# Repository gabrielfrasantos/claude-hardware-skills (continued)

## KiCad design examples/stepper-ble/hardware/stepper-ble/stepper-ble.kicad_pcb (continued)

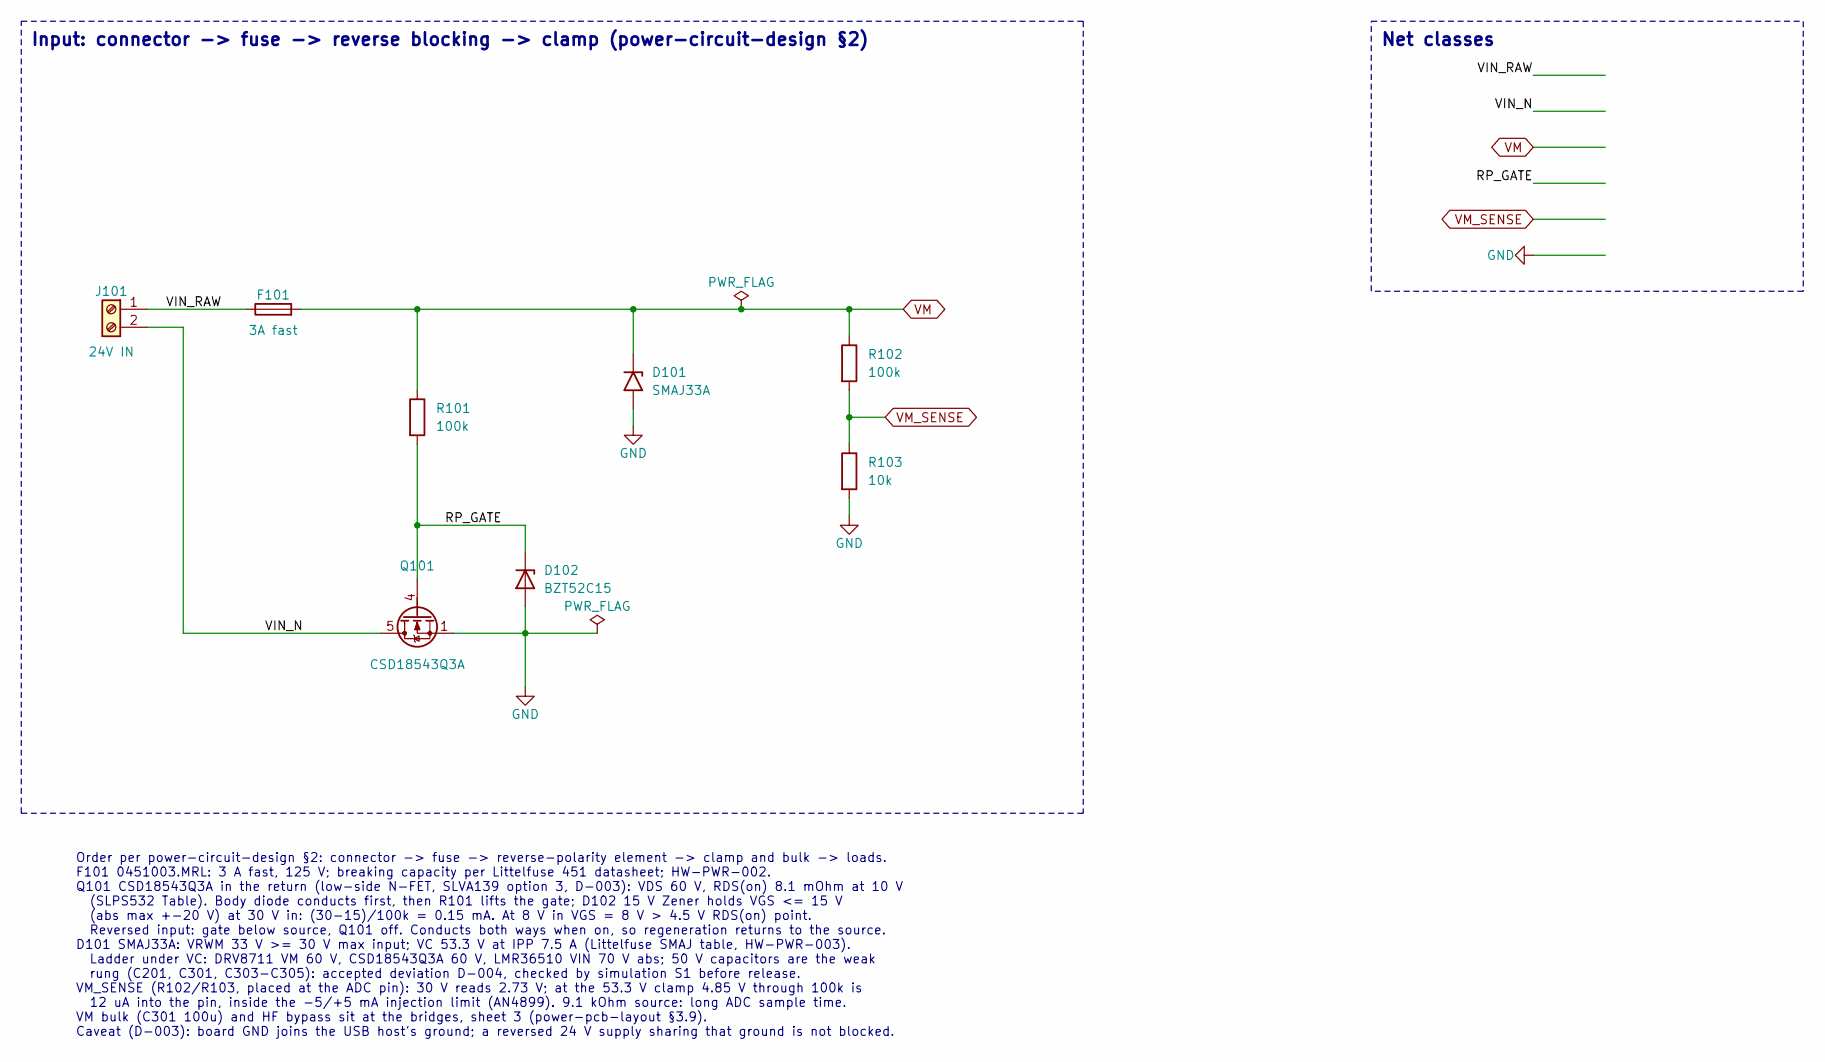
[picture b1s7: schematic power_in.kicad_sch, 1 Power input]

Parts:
D101: SMAJ33A; D_SMA; MPN SMAJ33A; LCSC C353454
D102: BZT52C15; D_SOD-123; MPN BZT52C15; LCSC C173427
F101: 3A fast; Fuse_Littelfuse-NANO2-451_453; Voltage 125V; MPN 0451003.MRL; LCSC C13982
J101: 24V IN; TerminalBlock_Phoenix_MKDS-1,5-2-5.08_1x02_P5.08mm_Horizont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; MPN 1715721; LCSC C480516
Q101: CSD18543Q3A; VSON-8_3.3x3.3mm_P0.65mm_NexFET_TI-land; Voltage 60V; MPN CSD18543Q3A; LCSC C840100
R101, R102: 100k; R_0402_1005Metric; MPN 0402WGF1003TCE; LCSC C25741
R103: 10k; R_0402_1005Metric; MPN 0402WGF1002TCE; LCSC C25744

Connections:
/1 Power input/RP_GATE: D102.1 (K), Q101.4 (G), R101.2
/1 Power input/VIN_N: J101.2, Q101.5 (D)
/1 Power input/VIN_RAW: F101.1, J101.1
GND: D101.2 (A2), D102.2 (A), Q101.1 (S), Q101.2 (S), Q101.3 (S), R103.2; also elsewhere on the board
VM: D101.1 (A1), F101.2, R101.1, R102.1; also elsewhere on the board
VM_SENSE: R102.2, R103.1; also elsewhere on the board

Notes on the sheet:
Input: connector -> fuse -> reverse blocking -> clamp (power-circuit-design §2)
Net classes
Order per power-circuit-design §2: connector -> fuse -> reverse-polarity element -> clamp and bulk -> loads. F101 0451003.MRL: 3 A fast, 125 V; breaking capacity per Littelfuse 451 datasheet; HW-PWR-002. Q101 CSD18543Q3A in the return (low-side N-FET, SLVA139 option 3, D-003): VDS 60 V, RDS(on) 8.1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

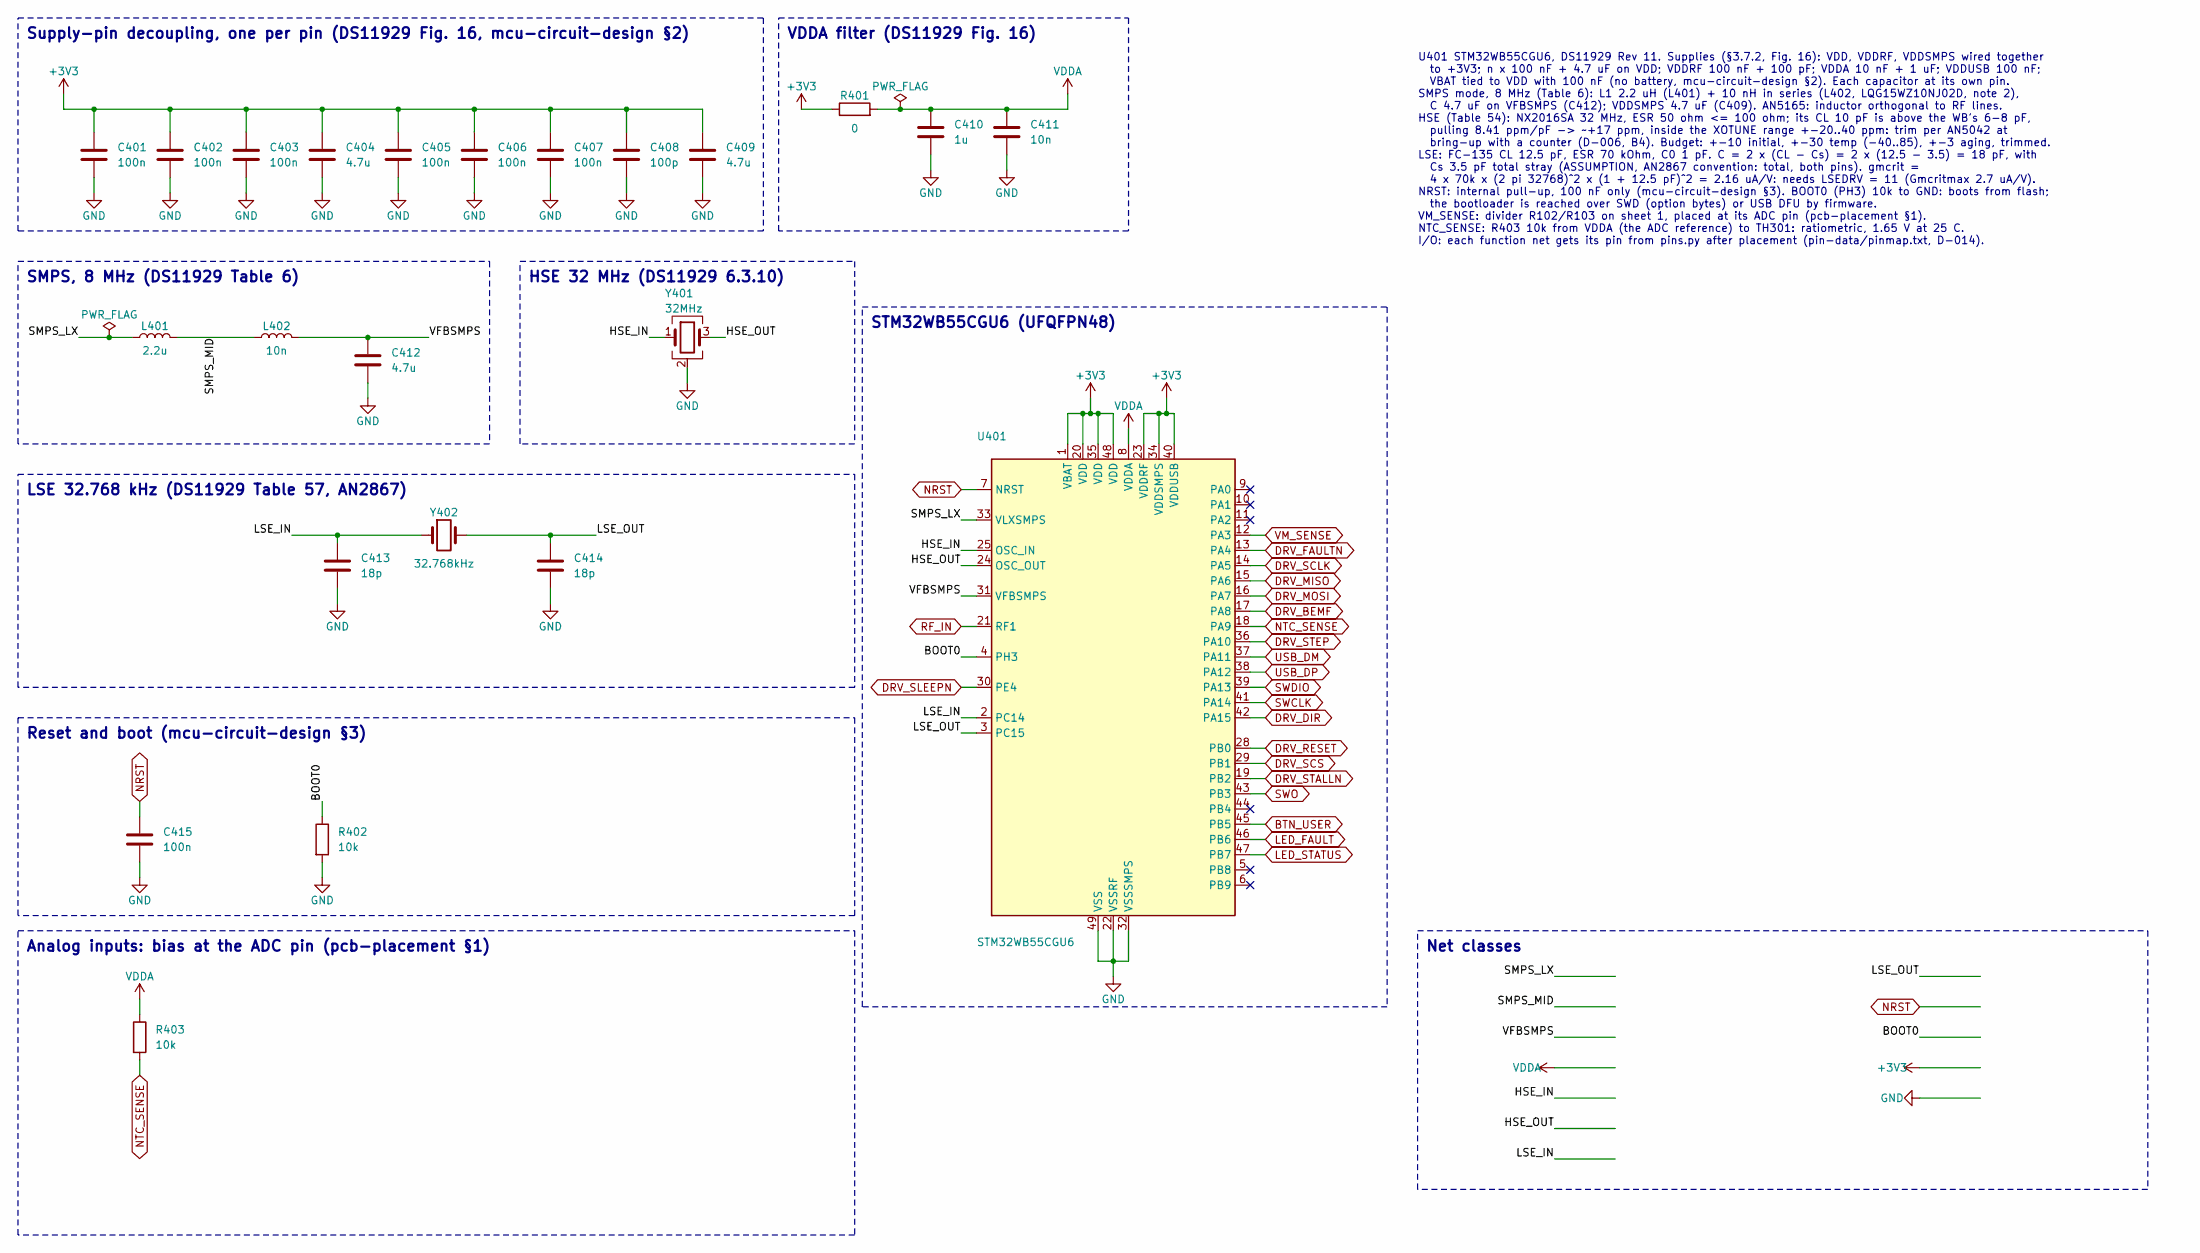
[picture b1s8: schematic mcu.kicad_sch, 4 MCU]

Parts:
C401, C402, C403, C405, C406, C407, C415: 100n; C_0402_1005Metric; Voltage 16V; MPN CL05B104KO5NNNC; LCSC C1525
C404, C409, C412: 4.7u; C_0402_1005Metric; Voltage 10V; MPN CL05A475MP5NRNC; LCSC C23733
C408: 100p; C_0402_1005Metric; Voltage 50V; MPN 0402CG101J500NT; LCSC C1546
C410: 1u; C_0402_1005Metric; Voltage 25V; MPN CL05A105KA5NNNC; LCSC C16193167
C411: 10n; C_0402_1005Metric; Voltage 50V; MPN CL05B103KB5NNNC; LCSC C15195
C413, C414: 18p; C_0402_1005Metric; Voltage 50V; MPN 0402CG180J500NT; LCSC C1549
L401: 2.2u; L_0805_2012Metric; MPN LQM21PN2R2MC0D; LCSC C98033
L402: 10n; L_0402_1005Metric; MPN LQG15WZ10NJ02D; LCSC C3911026
R401: 0; R_0402_1005Metric; MPN 0402WGF0000TCE; LCSC C17168
R402, R403: 10k; R_0402_1005Metric; MPN 0402WGF1002TCE; LCSC C25744
U401: STM32WB55CGU6; QFN-48-1EP_7x7mm_P0.5mm_EP5.6x5.6mm_ThermalVias; MPN STM32WB55CGU6; LCSC C404023
Y401: 32MHz; Crystal_SMD_2016-4Pin_2.0x1.6mm; MPN NX2016SA-32M-EXS00A-CS06465; LCSC C1986260
Y402: 32.768kHz; Crystal_SMD_3215-2Pin_3.2x1.5mm; MPN Q13FC13500004; LCSC C32346

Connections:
+3V3: C401.1, C402.1, C403.1, C404.1, C405.1, C406.1, C407.1, C408.1, C409.1, R401.1, U401.1 (VBAT), U401.20 (VDD), U401.23 (VDDRF), U401.34 (VDDSMPS), U401.35 (VDD), U401.40 (VDDUSB), U401.48 (VDD); also elsewhere on the board
/4 MCU/BOOT0: R402.1, U401.4 (PH3)
/4 MCU/HSE_IN: U401.25 (OSC_IN), Y401.1
/4 MCU/HSE_OUT: U401.24 (OSC_OUT), Y401.3
/4 MCU/LSE_IN: C413.1, U401.2 (PC14), Y402.1
/4 MCU/LSE_OUT: C414.1, U401.3 (PC15), Y402.2
/4 MCU/SMPS_LX: L401.1, U401.33 (VLXSMPS)
/4 MCU/SMPS_MID: L401.2, L402.1
/4 MCU/VFBSMPS: C412.1, L402.2, U401.31 (VFBSMPS)
BTN_USER: U401.45 (PB5); also elsewhere on the board
DRV_BEMF: U401.17 (PA8); also elsewhere on the board
DRV_DIR: U401.42 (PA15); also elsewhere on the board
DRV_FAULTN: U401.13 (PA4); also elsewhere on the board
DRV_MISO: U401.15 (PA6); also elsewhere on the board
DRV_MOSI: U401.16 (PA7); also elsewhere on the board
DRV_RESET: U401.28 (PB0); also elsewhere on the board
DRV_SCLK: U401.14 (PA5); also elsewhere on the board
DRV_SCS: U401.29 (PB1); also elsewhere on the board
DRV_SLEEPN: U401.30 (PE4); also elsewhere on the board
DRV_STALLN: U401.19 (PB2); also elsewhere on the board
DRV_STEP: U401.36 (PA10); also elsewhere on the board
GND: C401.2, C402.2, C403.2, C404.2, C405.2, C406.2, C407.2, C408.2, C409.2, C410.2, C411.2, C412.2, C413.2, C414.2, C415.2, R402.2, U401.22 (VSSRF), U401.32 (VSSSMPS), U401.49 (VSS), Y401.2 (G), Y401.4 (G); also elsewhere on the board
LED_FAULT: U401.46 (PB6); also elsewhere on the board
LED_STATUS: U401.47 (PB7); also elsewhere on the board
NRST: C415.1, U401.7 (NRST); also elsewhere on the board
NTC_SENSE: R403.2, U401.18 (PA9); also elsewhere on the board
RF_IN: U401.21 (RF1); also elsewhere on the board
SWCLK: U401.41 (PA14); also elsewhere on the board
SWDIO: U401.39 (PA13); also elsewhere on the board
SWO: U401.43 (PB3); also elsewhere on the board
USB_DM: U401.37 (PA11); also elsewhere on the board
USB_DP: U401.38 (PA12); also elsewhere on the board
VDDA: C410.1, C411.1, R401.2, R403.1, U401.8 (VDDA)
VM_SENSE: U401.12 (PA3); also elsewhere on the board

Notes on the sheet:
U401 STM32WB55CGU6, DS11929 Rev 11. Supplies (§3.7.2, Fig. 16): VDD, VDDRF, VDDSMPS wired together to +3V3; n x 100 nF + 4.7 uF on VDD; VDDRF 100 nF + 100 pF; VDDA 10 nF + 1 uF; VDDUSB 100 nF; VBAT tied to VDD with 100 nF (no battery, mcu-circuit-design §2). Each capacitor at its own pin. SMPS mode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
LSE 32.768 kHz (DS11929 Table 57, AN2867)
HSE 32 MHz (DS11929 6.3.10)
Supply-pin decoupling, one per pin (DS11929 Fig. 16, mcu-circuit-design §2)
STM32WB55CGU6 (UFQFPN48)
Reset and boot (mcu-circuit-design §3)
VDDA filter (DS11929 Fig. 16)
Net classes
Analog inputs: bias at the ADC pin (pcb-placement §1)
SMPS, 8 MHz (DS11929 Table 6)

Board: 4 copper layers, 106 parts (0 on the bottom side), 77 nets, no tracks yet.

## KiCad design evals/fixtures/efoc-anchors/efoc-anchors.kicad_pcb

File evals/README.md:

# Evals

Do the skills make Claude's hardware work better, and by how much? Each case runs the same task through headless
Claude Code **with** and **without** the plugin on a copy of a real board, and scores the result from the files against
the human baseline (the owner's own placement). See `docs/design.md` §5.

This folder is the **generic harness**. The **cases live in each board repo** (`<board-repo>/evals/cases/*.json`),
because the anchors and the commit to test belong to that board. Fixtures are built on demand from the board repo's
git history, so no board files are copied anywhere.

```bash
pip install -r evals/requirements.txt
python3 evals/test_evals.py                                          # self-test, no KiCad or Claude needed
python3 evals/make_fixture.py <board-repo>/evals/cases/placement.json # fixture only, to open in KiCad
python3 evals/run.py <board-repo>/evals --dry-run                    # the commands it would run
python3 evals/run.py <board-repo>/evals --case placement --runs 1    # one run per configuration
python3 evals/run.py <board-repo>/evals                              # everything, before a release tag
```

A placement run costs real money and can take up to an hour (`max_budget_usd` and `timeout_min` in each case).
Run it by hand, not in CI. Work directories go to `<board-repo>/evals/work/` (gitignore it there); summaries to
`<board-repo>/evals/results/`.

## KiCad 10 validation (docs/design.md §9, Phase B)

`validate_kicad.py` runs every script that writes a KiCad file on copies of a real board and has KiCad 10 load, DRC
and ERC each result. The board repo is not touched.

```bash
python3 evals/validate_kicad.py <board-repo> --out <dir> [--mcu U301 --needs pin-data/pin-needs.txt] [--pcbdoc reference/<x>.PcbDoc]
# Windows: add --kicad-cli "C:/Program Files/KiCad/10.0/bin/kicad-cli.exe"
python3 evals/test_validate_kicad.py        # self-test with a stand-in kicad-cli
```

It writes `<dir>/validation.md`: B0–B9 PASS / FAIL / SKIP with the evidence, and the few checks only the KiCad
window can show.

## Review: seeded defects

`review_defects.py` measures a design review on a real board, with no Claude run needed for the scripted part:

```bash
python3 evals/review_defects.py run <board.kicad_pcb> [--schematic root.kicad_sch] --voltage VBAT=12.6 --out <dir>
python3 evals/review_defects.py score <dir>/manifest.json --report <agent-review.md>   # score any review
python3 evals/test_review_defects.py                                                   # self-test
```

`run` plants one defect of each kind it finds a target for in a copy of the board and scores the scripted checks
on it. `score` grades any review (the board-reviewer agent's report, a human's) against the planted defects. See
`design-review` §5 for the defect kinds and the first measurements.

## A case

```json
{
  "kind": "placement",
  "source": {"commit": "<sha>", "board": "hardware/<name>/<name>.kicad_pcb"},
  "anchors": {"locked": true, "prefixes": ["J", "MH"], "refs": ["U301"]},
  "runs": 3, "timeout_min": 60, "max_budget_usd": 25
}
```

- `source`: the board at a pinned commit of the repo the case is in. Its `.kicad_pro` and `.kicad_dru` come along
  if they exist.
- `anchors`: `locked` takes the footprints the owner locked; `prefixes` and `refs` add parts by reference.
- `prompt` (optional): a built-in prompt (`prompts/<name>.md`, default: the `kind`) or a path relative to the case.

The fixture keeps the anchors (locked), parks every other footprint right of the outline, grouped by schematic
sheet, and drops tracks, vias, groups and copper zones (teardrops included); rule areas stay. `baseline.json` is the
source board's own score.

## Scores (`placement_metrics.py`, in the pcb-placement skill)

A run is **valid** when no anchor moved, every parked part is inside the outline, no courtyards overlap (real
outlines, so notches count) and no copper was added. For valid runs, lower is better:

- `ratsnest_mm`: sum over signal nets of the Manhattan minimum spanning tree of their pads;
- `crossings`: crossings between straight ratsnest edges of different nets, an estimate of vias and layer changes;
- `decap_p90_mm`: 90th percentile of the distance from a decoupling capacitor to the nearest IC pad on its net.

Ground and the nets the source board pours (`plane_nets` in the manifest) are left out: they are planes, not routes.
The summary gives each metric's median over valid runs and its ratio to the baseline. `within_limit` is the
placement gate's target (D25): ratsnest and crossings no worse than baseline × 1.10.

## Isolation

`run.py` starts Claude with `--setting-sources project` (the work directory has no project settings, so your user
settings and installed plugins don't load), `--strict-mcp-config` (no MCP servers) and, for `with-plugin` only,
`--plugin-dir plugins/hardware-design`. It keeps the stream-json transcript, and the results list the skills Claude
loaded, so a `without-plugin` run that loaded one of ours shows up. Flags checked against `claude --help` on
2026-11-20.

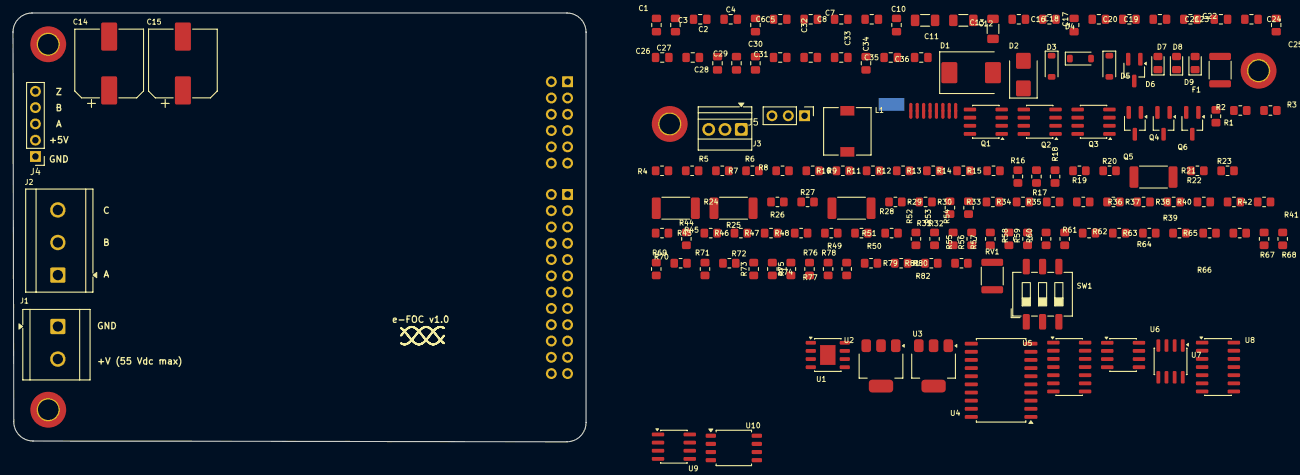
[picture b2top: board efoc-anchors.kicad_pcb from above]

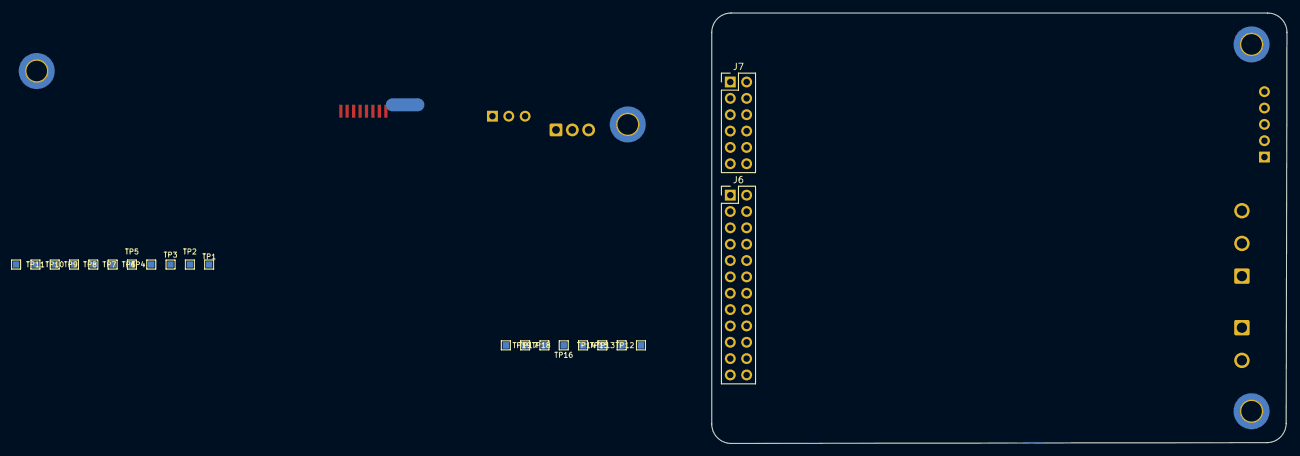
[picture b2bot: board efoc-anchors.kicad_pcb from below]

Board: 2 copper layers, 89.4 x 66.9 mm, 186 parts (22 on the bottom side), 128 nets, no tracks yet.

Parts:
C1: 2.2uF,100V,X7R; C_0805_2012Metric_Pad1.18x1.45mm_HandSolder
C2, C6: 2.2nF,50V,X7R; C_0805_2012Metric_Pad1.18x1.45mm_HandSolder
C3, C4, C7, C9, C10, C31: 100nF,50V,X7R; C_0805_2012Metric_Pad1.18x1.45mm_HandSolder
C5: 47pF,50V,X7R; C_0805_2012Metric_Pad1.18x1.45mm_HandSolder
C8: 4.7uF,50V,X7R; C_0805_2012Metric_Pad1.18x1.45mm_HandSolder
C11, C12, C13: 100nF,50V,X7R; C_1206_3216Metric_Pad1.33x1.80mm_HandSolder
C14, C15: 100uF/100V; CP_Elec_10x10.5
C16: 100nF,100V; C_0805_2012Metric_Pad1.18x1.45mm_HandSolder
C17, C18, C19: 100nF,16V; C_0805_2012Metric_Pad1.18x1.45mm_HandSolder
C20, C21, C22, C23, C24, C25, C26, C27: 150pF,50V; C_0805_2012Metric_Pad1.18x1.45mm_HandSolder
C28, C29, C35, C36: 100nF,16V,X7R; C_0805_2012Metric_Pad1.18x1.45mm_HandSolder
C30: 4.7nF; C_0805_2012Metric_Pad1.18x1.45mm_HandSolder
C32, C33, C34: 100pF,15V; C_0805_2012Metric_Pad1.18x1.45mm_HandSolder
D1: SMCJ51A; D_SMC
D2: 1SMB5945BT3G; D_SMB
D3, D4, D5: 1N4148W; D_SOD-123
D6: NUP2105L; SOT-23W_Handsoldering
D7, D8, D9: LED; LED_0805_2012Metric_Pad1.15x1.40mm_HandSolder
F1: Fuse; Fuse_1812_4532Metric
H1, H2, H3, H4: MountingHole; MountingHole_3.2mm_M3_DIN965_Pad_TopBottom
J1: Screw_Terminal_01x02; TerminalBlock_CUI_TB007-508-02_1x02_P5.08mm_Horizontal
J2: Screw_Terminal_01x03; TerminalBlock_CUI_TB007-508-03_1x03_P5.08mm_Horizontal
J3: Screw_Terminal_01x03; TerminalBlock_Xinya_XY308-2.54-3P_1x03_P2.54mm_Horizontal
J4: Conn_01x05_Pin; PinHeader_1x05_P2.54mm_Vertical
J5: Conn_01x03; PinHeader_1x03_P2.54mm_Vertical
J6: Conn_02x12_Odd_Even; PinHeader_2x12_P2.54mm_Vertical
J7: Conn_02x06_Odd_Even; PinHeader_2x06_P2.54mm_Vertical
L1: 100 uH; L_7.3x7.3_H4.5
NT1: NetTie_2; NetTie-2_SMD_Pad2.0mm
NT2, NT3, NT4, NT5, NT6, NT7, NT8, NT9: NetTie_3_Tee; NetTie-3_SMD_Pad0.5mm
Q1, Q2, Q3: CSD88537ND; SOIC-8_3.9x4.9mm_P1.27mm
Q4, Q5, Q6: BC847; SOT-23W_Handsoldering
R1: 124k; R_0805_2012Metric_Pad1.20x1.40mm_HandSolder
R2: 280k; R_0805_2012Metric_Pad1.20x1.40mm_HandSolder
R3: 576k; R_0805_2012Metric_Pad1.20x1.40mm_HandSolder
R4: 50k; R_0805_2012Metric_Pad1.20x1.40mm_HandSolder
R5: 33k; R_0805_2012Metric_Pad1.20x1.40mm_HandSolder
R6, R30, R31, R32: 100k; R_0805_2012Metric_Pad1.20x1.40mm_HandSolder
R7, R8, R9: 4K7; R_0805_2012Metric_Pad1.20x1.40mm_HandSolder
R10, R11, R12, R13, R14, R15, R34, R35, R37, R38, R40, R41, R46, R47, R52, R53, R54: 1k; R_0805_2012Metric_Pad1.20x1.40mm_HandSolder
R16, R17, R18: 10; R_0805_2012Metric_Pad1.20x1.40mm_HandSolder
R19, R20, R22, R23, R26, R27: 200; R_0805_2012Metric_Pad1.20x1.40mm_HandSolder
R21, R24, R25, R28: 0.02; R_2512_6332Metric_Pad1.40x3.35mm_HandSolder
R29: 2M; R_0805_2012Metric_Pad1.20x1.40mm_HandSolder
R33, R36, R39, R42, R43, R44, R45, R48, R61, R62, R63, R64, R65, R66, R67, R68, R70, R71, R72, R73, R75, R77: 10k; R_0805_2012Metric_Pad1.20x1.40mm_HandSolder
R49, R79, R80, R81, R82: 0R; R_0805_2012Metric_Pad1.20x1.40mm_HandSolder
R50, R51: 60R; R_0805_2012Metric_Pad1.20x1.40mm_HandSolder
R55, R56, R57: 100R; R_0805_2012Metric_Pad1.20x1.40mm_HandSolder
R58, R59, R60: 2k; R_0805_2012Metric_Pad1.20x1.40mm_HandSolder
R69: 22R; R_0805_2012Metric_Pad1.20x1.40mm_HandSolder
R74, R76, R78: 470R; R_0805_2012Metric_Pad1.20x1.40mm_HandSolder
RV1: Varistor; Fuse_1812_4532Metric
SW1: SW_DIP_x03; SW_DIP_SPSTx03_Slide_6.7x9.18mm_W8.61mm_P2.54mm_LowProfile
TP1, TP2, TP3, TP4, TP5, TP6, TP7, TP8, TP9, TP10, TP11, TP12, TP13, TP14, TP15, TP16, TP17, TP18, TP19: TestPoint; TestPoint_Pad_1.0x1.0mm
U1: LM5164DDA; HSOP-8-1EP_3.9x4.9mm_P1.27mm_EP2.41x3.1mm
U2: LM317_SOT-223; SOT-223-3_TabPin2
U3: AMS1117-3.3; SOT-223-3_TabPin2
U4: FAN7888; SOIC-20W_7.5x12.8mm_P1.27mm
U5: TLV9064; SOIC-14_3.9x8.7mm_P1.27mm
U6: TLV9062; SOIC-8_3.9x4.9mm_P1.27mm
U7: SN65HVD230; SOIC-8_3.9x4.9mm_P1.27mm
U8: 74LVC14; SOIC-14_3.9x8.7mm_P1.27mm
U9: 24LC04; SOIC-8_3.9x4.9mm_P1.27mm
U10: W25Q32JVSS; SOIC-8_5.3x5.3mm_P1.27mm

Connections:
+3.3V: C7.1, C17.1, C19.1, C29.1, C31.1, C35.1, C36.1, D7.2 (A), D8.2 (A), D9.2 (A), J6.2, J7.2, R31.1, R61.1, R63.1, R65.1, R67.1, R68.1, R70.2, R71.2, R72.1, TP4.1 (1_1), U3.2 (VO), U5.4 (V+), U6.8 (V+), U7.3 (VCC), U8.14 (3.3V), U9.8 (VCC), U10.8 (VCC)
+5V: C4.1, C9.1, J4.2, R5.1, R52.1, R53.1, R54.1, TP5.1 (1_1), U2.2 (VO), U3.3 (VI)
+15V: C3.1, C6.1, C8.1, C10.1, L1.2, R3.1, R16.2, R17.2, R18.2, TP3.1 (1_1), U2.3 (VI), U4.12 (VDD)
/adc-conditioner/ADC_MIDPOINT: C20.1, C21.1, C22.1, C26.1, R33.2, R36.2, R39.2, R45.2, TP15.1 (1_1), U5.1, U5.2 (-)
/adc-conditioner/CUR_A: C23.1, J6.8, R42.1, TP16.1 (1_1), U5.7
/adc-conditioner/CUR_A_N: NT3.3, R34.2
/adc-conditioner/CUR_A_P: NT2.3, R35.2
/adc-conditioner/CUR_B: C24.1, J6.6, R43.1, TP17.1 (1_1), U5.8
/adc-conditioner/CUR_B_N: NT5.3, R37.2
/adc-conditioner/CUR_C: C25.1, J6.5, R44.1, TP18.1 (1_1), U5.14
/adc-conditioner/CUR_C_N: NT9.3, R40.2
/adc-conditioner/CUR_C_P: NT8.3, R41.2
/adc-conditioner/CUR_TOTAL: C27.1, J6.4, R48.1, TP19.1 (1_1), U6.1
/adc-conditioner/CUR_TOTAL_N: NT7.3, R47.2
/adc-conditioner/CUR_TOTAL_P: NT6.3, R46.2
/adc-conditioner/CUR­_B_P: NT4.3, R38.2
/adc-conditioner/VOLT_TOTAL: J6.3, U6.6 (-), U6.7
/can-bus/CAN_RX: J6.15, U7.4 (R)
/can-bus/CAN_TX: J6.18, U7.1 (D)
/driver/HO1: R19.2, U4.19 (HO1)
/driver/HO2: R22.2, U4.15 (HO2)
/driver/HO3: R26.2, U4.9 (HO3)
/driver/LO1: R20.2, U4.17 (LO1)
/driver/LO2: R23.2, U4.13 (LO2)
/driver/LO3: R27.2, U4.7 (LO3)
/driver/PWM_A_H: J6.23, R10.2, TP6.1 (1_1)
/driver/PWM_A_L: J6.24, R7.1, R11.2, TP9.1 (1_1)
/driver/PWM_B_H: J6.21, R12.2, TP7.1 (1_1)
/driver/PWM_B_L: J6.22, R8.1, R13.2, TP10.1 (1_1)
/driver/PWM_C_H: J6.19, R14.2, TP8.1 (1_1)
/driver/PWM_C_L: J6.20, R9.1, R15.2, TP11.1 (1_1)
/driver/VS1: C11.2, J2.1, Q1.1 (S), Q1.5 (D), Q1.6 (D), TP14.1 (1_1), U4.18 (VS1)
/driver/VS2: C12.2, J2.2, Q2.1 (S), Q2.5 (D), Q2.6 (D), TP13.1 (1_1), U4.14 (VS2)
/driver/VS3: C13.2, J2.3, Q3.1 (S), Q3.5 (D), Q3.6 (D), TP12.1 (1_1), U4.8 (VS3)
/eeprom-mem/I2C_SCL: J6.13, R68.2, U9.6 (SCL)
/eeprom-mem/I2C_SDA: J6.16, R67.2, U9.5 (SDA)
/encoder/ENC_A: J7.6, U8.8
/encoder/ENC_B: J7.8, U8.10
/encoder/ENC_C: J7.7, U8.12
/flash-mem/SPI_CS: J6.7, R72.2, U10.1 (~CS)
/flash-mem/SPI_MISO: R79.2, R80.2, U10.5 (DI/IO_{0})
/flash-mem/SPI_MOSI: R81.2, R82.2, U10.2 (DO/IO_{1})
/flash-mem/SPI_SCK: J6.10, R69.2
/microcontroller-connector/BTN_1: J7.5, SW1.1
/microcontroller-connector/BTN_2: J7.4, SW1.2
/microcontroller-connector/BTN_3: J7.3, SW1.3
/microcontroller-connector/LED_B: J7.12, R77.1
/microcontroller-connector/LED_G: J7.9, R75.1
/microcontroller-connector/LED_R: J7.10, R73.1
/microcontroller-connector/POWER_GOOD: J6.17, TP2.1 (1_1), U1.6 (PGOOD)
GND: C3.2, C4.2, C7.2, C8.2, C9.2, C17.2, C18.2, C19.2, C28.2, C29.2, C30.2, C31.2, C32.2, C33.2, C34.2, C35.2, C36.2, D6.3 (A), J3.2, J4.1, J5.1, J6.1, J7.1, J7.11, NT1.1, Q4.2 (E), Q5.2 (E), Q6.2 (E), R6.2, R7.2, R8.2, R9.2, R32.2, R49.2, R62.2, R64.2, R66.2, SW1.4, SW1.5, SW1.6, U3.1 (GND), U5.11 (V-), U6.4 (V-), U7.2 (GND), U8.7 (GND), U9.4 (GND), U9.7 (WP), U10.4 (GND)
GNDPWR: C1.2, C10.2, C14.2, C15.2, C16.2, D1.2 (A2), D2.2 (A), J1.1, NT1.2, NT7.1, NT7.2, R1.2, R4.2, R25.2, R30.2, RV1.2, U1.1 (GND), U1.9 (EP), U4.11 (GND)
unnamed: C5.1, C6.2, R2.1
unnamed: C30.1, R50.2, R51.1
unnamed: C32.1, R55.1, R58.2
unnamed: C33.1, R56.1, R59.2
unnamed: C34.1, R57.1, R60.2
unnamed: D3.2 (A), R16.1
unnamed: C13.1, D3.1 (K), U4.10 (VB3)
unnamed: D4.2 (A), R17.1
unnamed: C12.1, D4.1 (K), U4.16 (VB2)
unnamed: D5.2 (A), R18.1
unnamed: C11.1, D5.1 (K), U4.20 (VB1)
unnamed: D7.1 (K), R74.2
unnamed: D8.1 (K), R76.2
unnamed: D9.1 (K), R78.2
unnamed: F1.2, J1.2
unnamed: D6.2 (K), J3.1, R50.1, U7.7 (CANH)
unnamed: D6.1 (K), J3.3, R51.2, U7.6 (CANL)
unnamed: J4.3, R52.2, R55.2
unnamed: J4.4, R53.2, R56.2
unnamed: J4.5, R54.2, R57.2
unnamed: J5.2, J6.11
unnamed: J5.3, J6.9
unnamed: J6.12, R79.1, R82.1
unnamed: J6.14, R80.1, R81.1
unnamed: NT2.1, NT2.2, Q1.3 (S), R21.1
unnamed: NT3.1, NT3.2, NT5.1, NT5.2, NT6.1, NT6.2, NT9.1, NT9.2, R21.2, R24.2, R25.1, R28.2
unnamed: NT4.1, NT4.2, Q2.3 (S), R24.1
unnamed: NT8.1, NT8.2, Q3.3 (S), R28.1
unnamed: Q1.2 (G), R19.1
unnamed: Q1.4 (G), R20.1
unnamed: Q2.2 (G), R22.1
unnamed: Q2.4 (G), R23.1
unnamed: Q3.2 (G), R26.1
unnamed: Q3.4 (G), R27.1
unnamed: Q4.1 (B), R73.2
unnamed: Q4.3 (C), R74.1
unnamed: Q5.1 (B), R75.2
unnamed: Q5.3 (C), R76.1
unnamed: Q6.1 (B), R77.2
unnamed: Q6.3 (C), R78.1
unnamed: R58.1, U8.1
unnamed: R59.1, U8.3
unnamed: R60.1, U8.5
unnamed: C2.2, U1.7 (BST)
unnamed: C5.2, R3.2, R4.1, U1.5 (FB)
unnamed: R1.1, U1.4 (RON)
unnamed: C2.1, L1.1, R2.2, U1.8 (SW)
unnamed: R5.2, R6.1, U2.1 (ADJ)
unnamed: R10.1, U4.1 (HIN1)
unnamed: R12.1, U4.3 (HIN2)
unnamed: R14.1, U4.5 (HIN3)
unnamed: R11.1, U4.2 (LIN1)
unnamed: R13.1, U4.4 (LIN2)
unnamed: R15.1, U4.6 (LIN3)
unnamed: C18.1, R31.2, R32.1, U5.3 (+)
unnamed: C20.2, R33.1, R34.1, U5.5 (+)
unnamed: C23.2, R35.1, R42.2, U5.6 (-)
unnamed: C21.2, R36.1, R37.1, U5.10 (+)
unnamed: C24.2, R38.1, R43.2, U5.9 (-)
unnamed: C22.2, R39.1, R40.1, U5.12 (+)
unnamed: C25.2, R41.1, R44.2, U5.13 (-)
unnamed: C26.2, R45.1, R46.1, U6.3 (+)
unnamed: C27.2, R47.1, R48.2, U6.2 (-)
unnamed: C16.1, R29.2, R30.1, U6.5 (+)
unnamed: R49.1, U7.8 (Rs)
unnamed: C28.1, U7.5 (Vref)
unnamed: U8.2, U8.9
unnamed: U8.4, U8.11
unnamed: U8.6, U8.13
unnamed: R65.2, R66.1, U9.1 (A0)
unnamed: R63.2, R64.1, U9.2 (A1)
unnamed: R61.2, R62.1, U9.3 (A2)
unnamed: R69.1, U10.6 (CLK)
unnamed: R71.1, U10.7 (~HOLD/~RESET/IO_{3})
unnamed: R70.1, U10.3 (~WP/IO_{2})
Vdrive: C1.1, C14.1, C15.1, D1.1 (A1), D2.1 (K), F1.1, Q1.7 (D), Q1.8 (D), Q2.7 (D), Q2.8 (D), Q3.7 (D), Q3.8 (D), R29.1, RV1.1, TP1.1 (1_1), U1.2 (VIN), U1.3 (EN/UVLO)
